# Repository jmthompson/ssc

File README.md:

# Simple Serial Card

## Overview

The Simple Serial Card is a low-cost Super Serial Card work-a-like. I designed
this because I needed a way to use ADTPro on my Apple IIe, and the price of
super serial cards on eBay is getting a bit high for my taste.

This card is more or less 100% compatible with the original Apple card. It
uses the same 6551 ACIA mapped to the same I/O locations, and in fact can
use the same firmware ROM.  It does however have some minor differences in the
interest of cost:

1. There are no DIP switches, so you cannot set the default configuration. It
   does, however, include a jumper that can be removed to disable IRQs.
2. Instead of a DB-25 it is wired to use a DB-9 cable like those used by PC
   motherboards.
3. There is no terminal/modem block to change the serial port wiring. Just use
   the appropriate cable instead, or a null modem adapter.

The KiCAD schematics and PCB layout are included. It is a four layer board,
because my fab house of choice charges the same for 2 and 4 layers, so I went
with what made the layout easier.

## Parts List

* A 74LS245 octal bus transceiver (non-TTL appears to have issues with the ROM address decode logic) (U1)
* A 28C256 EEPROM (28-pin JEDEC EPROMs such as the 27128 also work) (U2)
* A 1.8432 MHz 5V oscillator (U3)
* A 22V10 GAL (any speed or variety should work) (U4)
* A W65C51N ACIA (U5)
* Two MAX3232 RS-232 line transceivers (U6, U7)
* Seven 0.1uf ceramic bypass caps (C1-C7)
* Eight 1uf 16V electrolytic caps (C9-C16)
* A 2x5 pin header (J1)
* A 1x2 pin header (J2)

## Assembly

Before assembly you will need to burn firmware ROM into the EEPROM, and burn
the appropriat equations into the GAL. See "Burning the ROM" and "Burning the
GAL" below for more details.

I would suggest socketing all of the chips, but at the very least socket the
ROM and the GAL in case you need to update them.

As mentioned above the header on this card is wired the same as a PC COM
header. There are two varieties of these cables available; this card uses the
newer style which is wired 1:1; that is, pin 1 on the header goes to pin 1
on the DB-9, pin 2 to pin 2, etc. These are sometimes referred to as
"AT/EVEREX" style cables.

There is an asterisk on the card's silkscreen indicating pin one on the RS-232
header; make sure this lines up with pin one on your ribbon cable. Usually this
is the red wire on the ribbon cable.

## Installation

Turn off the computer, put the card in an empty slot, and mount the DB-9 on one
of the small cutouts on the back of the computer (or just run the ribbon cable
through an open cutout if you don't care).

## Design Considerations

Many parts choices were influenced by what I have already in my parts bin, even
if that makes the design non-optimal. For example, I used MAX3232 line drivers
because I have a ton of them. With 12V available on the slots I could've used
different parts and avoided all the charge pump caps, but I didn't feel like
buying more chips.

With the exception of the 22V10 GAL used for glue logic all parts in this design
are still actively available. The GALs are out of production but still readily
available on eBay or Aliexpress (though YMMV as far as quality).

## Burning the ROM

A standard super serial card image should work fine with this card, though
since there are no configuration switches the default settings after power on
or reset will be somewhat random.  Once I have working cards built I will be
creating a customized firmware ROM that sets the defaults to 9600 bps for the
ADT Pro bootstrap.

Since 2K EPROMs are nearly impossible to find I subbed in an AT28C256 EEPROM
(again, I had one already). Only the lower 2K is used by the card, so when
burning you can either duplicate the image 16 times, or fill the upper 30K
with zeroes or some other random data. In theory a AT28C64 EEPROM should also
work (and only waste 6K), but I don't have one to test, and a brief search
suggests they aren't any cheaper than the AT28C256 (presumably because they
are out of production).

I use the TL866 II+ USB programmer along with the minipro Linux client for my
ROM burns.

## Burning the GAL

The equations for the GAL are included as a .pld file for the GALasm program.
If you run Linux or another OS that can run GNU make then you should be able
to just type "make" in the "gal" subfolder to compile the equations into a
.jed file.  Burning this file requires a suitable programmer; I personally
use the same TL866 II+ that I use for burning ROMs, though at least at the time
of this writing the minipro client doesn't know how to burn GALs properly, so
you'll need to use the official client software, either on a Windows PC or
under Wine.

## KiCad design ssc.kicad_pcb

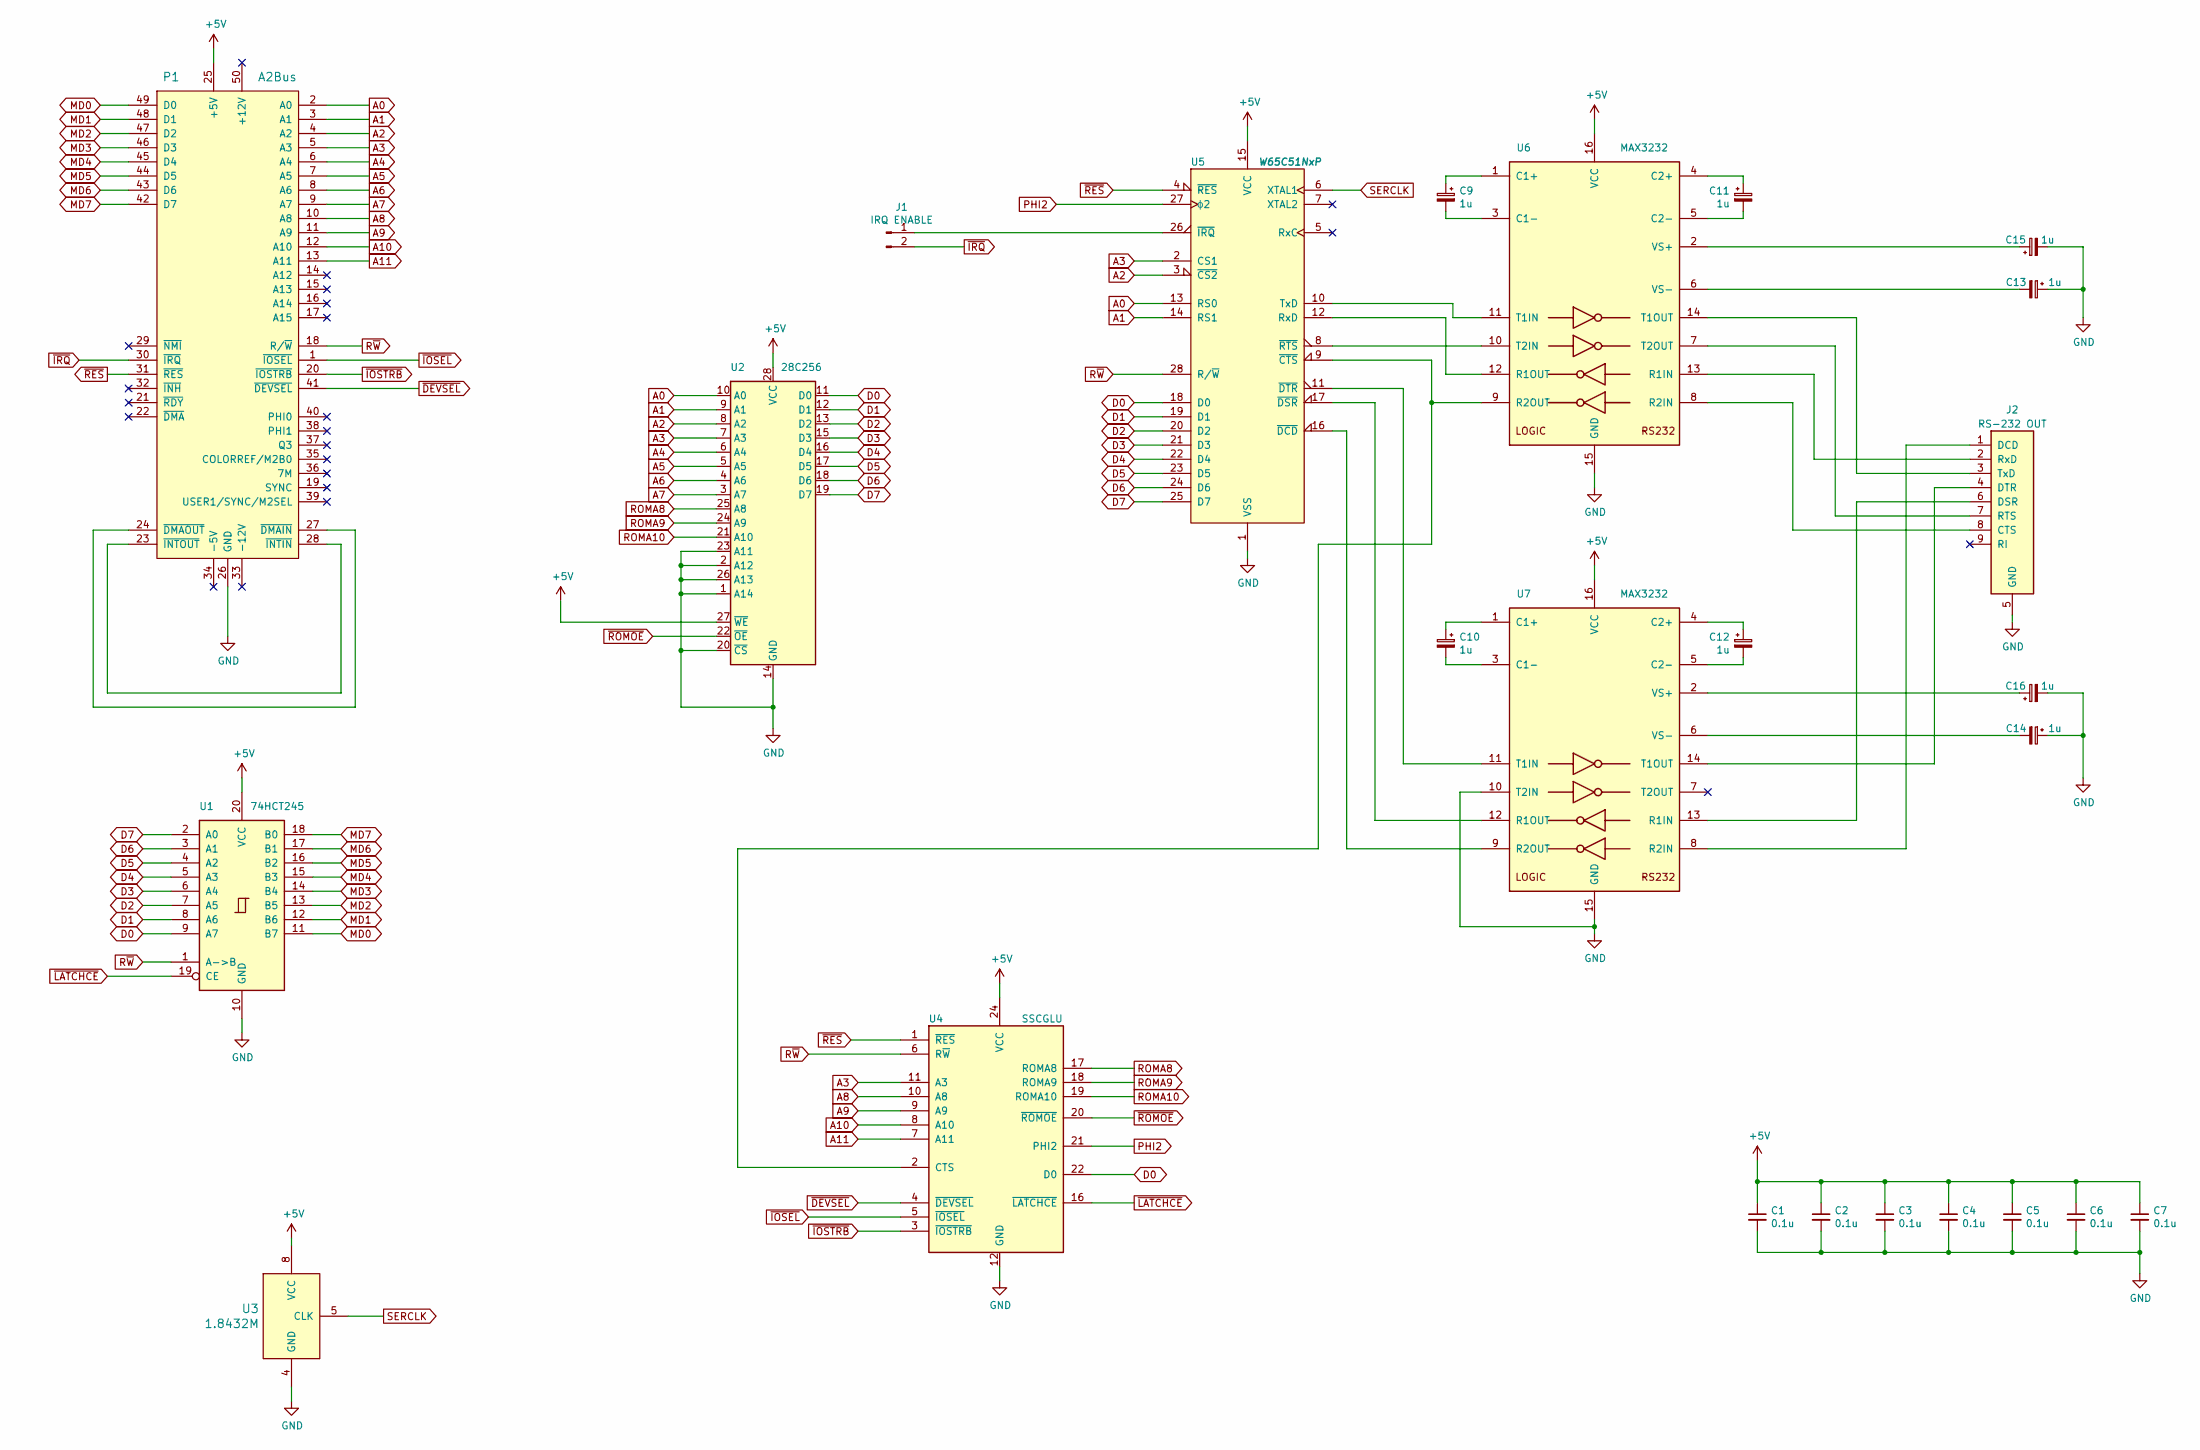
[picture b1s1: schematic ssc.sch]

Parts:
C1, C2, C3, C4, C5, C6, C7: 0.1u; C_Disc_D4.3mm_W1.9mm_P5.00mm
C9, C10, C11, C12, C13, C14, C15, C16: 1u; CP_Radial_D5.0mm_P2.50mm
J1: IRQ ENABLE; PinHeader_1x02_P2.54mm_Vertical
J2: RS-232 OUT; PinHeader_2x05_P2.54mm_Vertical
P1: A2Bus; Male_Card-Edge_50_pin__100_mil
U1: 74HCT245; DIP-20_W7.62mm_Socket
U2: 28C256; DIP-28_W15.24mm_Socket
U3: 1.8432M; DIP-8_W7.62mm_Socket
U4: SSCGLU; DIP-24_W7.62mm_Socket
U5: W65C51NxP; DIP-28_W15.24mm_Socket
U6, U7: MAX3232; DIP-16_W7.62mm_Socket

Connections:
+5V: C1.1, C2.1, C3.1, C4.1, C5.1, C6.1, C7.1, P1.25 (+5V), U1.20 (VCC), U2.27 (~WE), U2.28 (VCC), U3.8 (VCC), U4.24 (VCC), U5.15 (VCC), U6.16 (VCC), U7.16 (VCC)
A0: P1.2 (A0), U2.10 (A0), U5.13 (RS0)
A1: P1.3 (A1), U2.9 (A1), U5.14 (RS1)
A2: P1.4 (A2), U2.8 (A2), U5.3 (~CS2)
A3: P1.5 (A3), U2.7 (A3), U4.11 (A3), U5.2 (CS1)
A4: P1.6 (A4), U2.6 (A4)
A5: P1.7 (A5), U2.5 (A5)
A6: P1.8 (A6), U2.4 (A6)
A7: P1.9 (A7), U2.3 (A7)
A8: P1.10 (A8), U4.10 (A8)
A9: P1.11 (A9), U4.9 (A9)
A10: P1.12 (A10), U4.8 (A10)
A11: P1.13 (A11), U4.7 (A11)
D0: U1.9 (A7), U2.11 (D0), U4.22 (D0), U5.18 (D0)
D1: U1.8 (A6), U2.12 (D1), U5.19 (D1)
D2: U1.7 (A5), U2.13 (D2), U5.20 (D2)
D3: U1.6 (A4), U2.15 (D3), U5.21 (D3)
D4: U1.5 (A3), U2.16 (D4), U5.22 (D4)
D5: U1.4 (A2), U2.17 (D5), U5.23 (D5)
D6: U1.3 (A1), U2.18 (D6), U5.24 (D6)
D7: U1.2 (A0), U2.19 (D7), U5.25 (D7)
GND: C1.2, C2.2, C3.2, C4.2, C5.2, C6.2, C7.2, C13.1, C14.1, C15.2, C16.2, J2.5 (GND), P1.26 (GND), U1.10 (GND), U2.1 (A14), U2.2 (A12), U2.14 (GND), U2.20 (~CS), U2.23 (A11), U2.26 (A13), U3.4 (GND), U4.12 (GND), U5.1 (VSS), U6.15 (GND), U7.10 (T2IN), U7.15 (GND)
MD0: P1.49 (D0), U1.11 (B7)
MD1: P1.48 (D1), U1.12 (B6)
MD2: P1.47 (D2), U1.13 (B5)
MD3: P1.46 (D3), U1.14 (B4)
MD4: P1.45 (D4), U1.15 (B3)
MD5: P1.44 (D5), U1.16 (B2)
MD6: P1.43 (D6), U1.17 (B1)
MD7: P1.42 (D7), U1.18 (B0)
unnamed: C9.1, U6.1 (C1+)
unnamed: C9.2, U6.3 (C1-)
unnamed: C10.1, U7.1 (C1+)
unnamed: C10.2, U7.3 (C1-)
unnamed: C11.1, U6.4 (C2+)
unnamed: C11.2, U6.5 (C2-)
unnamed: C12.1, U7.4 (C2+)
unnamed: C12.2, U7.5 (C2-)
unnamed: C13.2, U6.6 (VS-)
unnamed: C14.2, U7.6 (VS-)
unnamed: C15.1, U6.2 (VS+)
unnamed: C16.1, U7.2 (VS+)
unnamed: J1.1, U5.26 (~IRQ)
unnamed: J2.1 (DCD), U7.8 (R2IN)
unnamed: J2.2 (RxD), U6.13 (R1IN)
unnamed: J2.3 (TxD), U6.14 (T1OUT)
unnamed: J2.4 (DTR), U7.14 (T1OUT)
unnamed: J2.6 (DSR), U7.13 (R1IN)
unnamed: J2.7 (RTS), U6.7 (T2OUT)
unnamed: J2.8 (CTS), U6.8 (R2IN)
unnamed: P1.23 (~INTOUT), P1.28 (~INTIN)
unnamed: P1.24 (~DMAOUT), P1.27 (~DMAIN)
unnamed: U4.2 (CTS), U5.9 (~CTS), U6.9 (R2OUT)
unnamed: U5.8 (~RTS), U6.10 (T2IN)
unnamed: U5.10 (TxD), U6.11 (T1IN)
unnamed: U5.11 (~DTR), U7.11 (T1IN)
unnamed: U5.12 (RxD), U6.12 (R1OUT)
unnamed: U5.16 (~DCD), U7.9 (R2OUT)
unnamed: U5.17 (~DSR), U7.12 (R1OUT)
PHI2: U4.21 (PHI2), U5.27 (ϕ2)
ROMA8: U2.25 (A8), U4.17 (ROMA8)
ROMA9: U2.24 (A9), U4.18 (ROMA9)
ROMA10: U2.21 (A10), U4.19 (ROMA10)
R~W: P1.18 (R/~W), U1.1 (A->B), U4.6 (R~W), U5.28 (R/~W)
SERCLK: U3.5 (CLK), U5.6 (XTAL1)
~DEVSEL: P1.41 (~DEVSEL), U4.4 (~DEVSEL)
~IOSEL: P1.1 (~IOSEL), U4.5 (~IOSEL)
~IOSTRB: P1.20 (~IOSTRB), U4.3 (~IOSTRB)
~IRQ: J1.2, P1.30 (~IRQ)
~LATCHCE: U1.19 (CE), U4.16 (~LATCHCE)
~RES: P1.31 (~RES), U4.1 (~RES), U5.4 (~RES)
~ROMOE: U2.22 (~OE), U4.20 (~ROMOE)

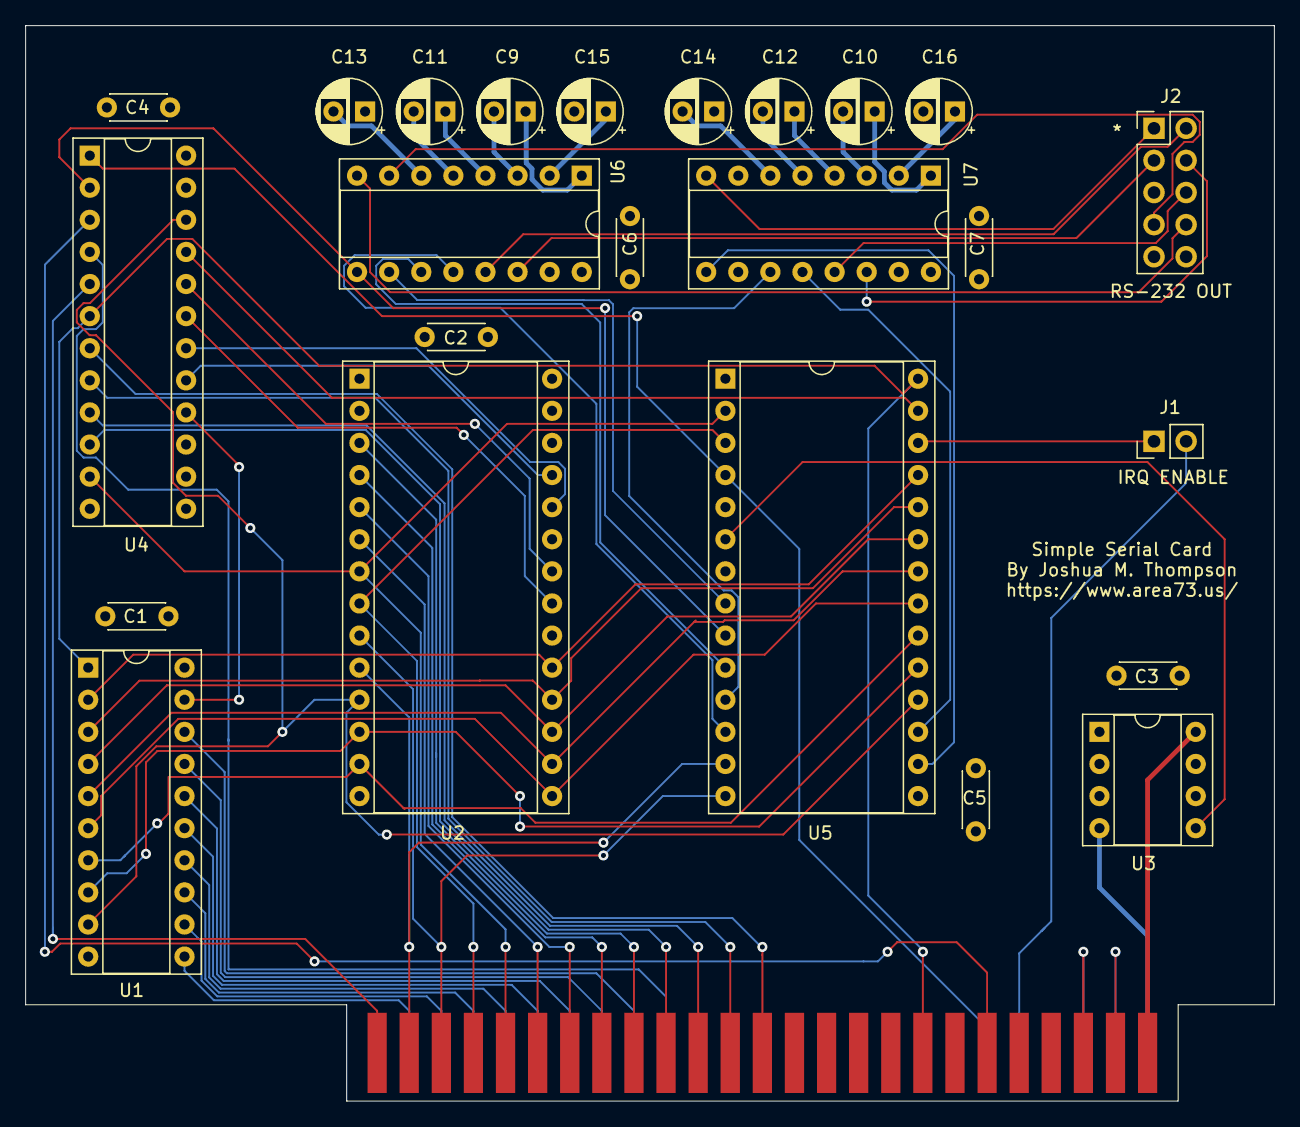
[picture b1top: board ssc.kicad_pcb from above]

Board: 4 copper layers, 98.8 x 85.1 mm, 25 parts (0 on the bottom side), 72 nets.

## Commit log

2021-04-03 - Updated schematic, mostly tweaks to make layout easier. - Updated GAL equations - Add PCBNew layout for initial test run
2021-04-03 Updated the README
2023-03-09 Add working PLD file and JED file generated therewith.
2023-03-09 Sync to tested version.
2023-03-09 CMOS logic for the bus transceiver appears to have issues with ROM decode.
2023-03-09 Add latest .jed
2023-03-09 Add patch mechanism for ROM.
2023-03-10 Snarf SSC ROM from mirror for patching.
2023-03-10 Note that JEDEC EPROMs also work.
